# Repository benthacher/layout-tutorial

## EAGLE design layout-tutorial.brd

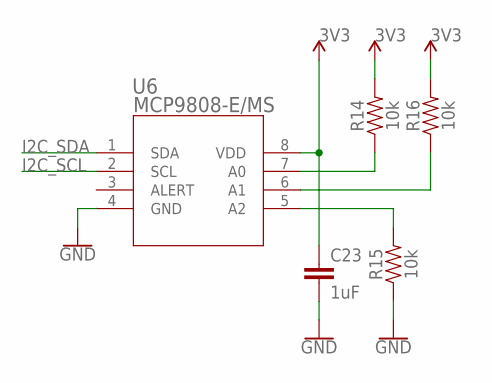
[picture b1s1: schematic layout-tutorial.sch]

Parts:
C23: 1uF; 0603@1
R14, R15, R16: 10k; 0603
U6: MCP9808-E/MS; MSOP8_MC

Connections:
3V3: C23.1, R14.2, R16.2, U6.8 (VDD)
GND: C23.2, R15.1, U6.4 (GND)
I2C_SCL: U6.2 (SCL)
I2C_SDA: U6.1 (SDA)
unnamed: R15.2, U6.5 (A2)
unnamed: R16.1, U6.6 (A1)
unnamed: R14.1, U6.7 (A0)

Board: 2 copper layers, 5 parts (0 on the bottom side), 5 nets, no tracks yet.

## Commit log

2021-12-09 Wow windows 11

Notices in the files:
parts and their libraries:
SparkFun-Capacitors: Licensing: Creative Commons ShareAlike 4.0 International - https://creativecommons.org/licenses/by-sa/4.0
